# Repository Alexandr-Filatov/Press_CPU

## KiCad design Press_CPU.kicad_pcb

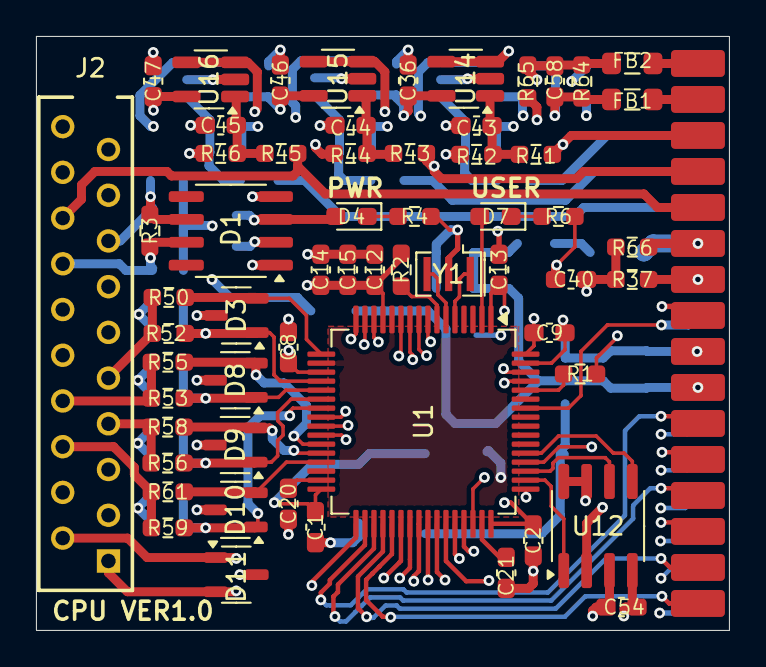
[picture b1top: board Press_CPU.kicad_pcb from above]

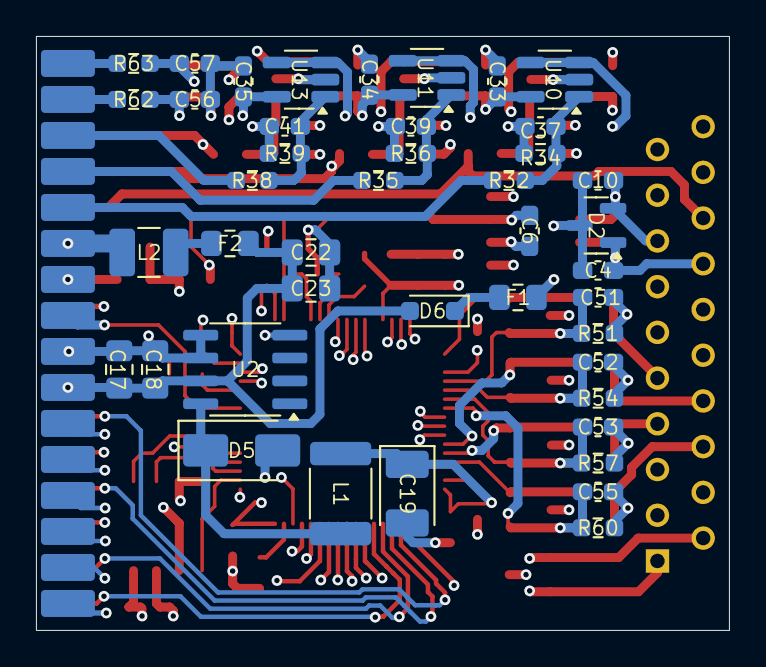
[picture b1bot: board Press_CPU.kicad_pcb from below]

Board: 6 copper layers, 38.5 x 33.0 mm, 104 parts (44 on the bottom side), 79 nets.

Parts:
C1, C2, C8, C9, C12, C13, C33, C34, C35, C36, C46, C47, C51, C52, C53, C55, C56, C57: 100n; C_0603_1608Metric_Pad1.08x0.95mm_HandSolder
C4, C10: 56p; C_0603_1608Metric_Pad1.08x0.95mm_HandSolder
C6, C20, C21, C58: 2.2u; C_0603_1608Metric_Pad1.08x0.95mm_HandSolder
C14: 4.7u; C_0603_1608Metric_Pad1.08x0.95mm_HandSolder
C15, C54: 1u; C_0603_1608Metric_Pad1.08x0.95mm_HandSolder
C17, C18, C22, C23: 10u; C_0805_2012Metric_Pad1.18x1.45mm_HandSolder
C19: 100u; CP_EIA-3528-21_Kemet-B_HandSolder
C37, C39, C40, C41, C43, C44, C45: 1n; C_0603_1608Metric_Pad1.08x0.95mm_HandSolder
D1: SOIC-8_3.9x4.9mm_P1.27mm
D2: SOT-23
D3, D8, D9, D10, D11: GSOT03C-E3-08; SOT-23-3
D4, D7: LED_0603_1608Metric_Pad1.05x0.95mm_HandSolder
D5: MBRA320; D_SMA
D6: D_Schottky_Small; D_SOD-323_HandSoldering
F1, F2: Fuse_Small; Fuse_0805_2012Metric_Pad1.15x1.40mm_HandSolder
FB1, FB2: BLM21AG102SN1D; L_0805_2012Metric_Pad1.05x1.20mm_HandSolder
J2: 2-215079-0; 22150790
J3, J4: Conn_01x16; PLD16_2.0mm
L1: 47u; L_1812_4532Metric_Pad1.30x3.40mm_HandSolder
L2: 2.2u; L_1210_3225Metric_Pad1.42x2.65mm_HandSolder
R1, R2, R6: 1k; R_0603_1608Metric_Pad0.98x0.95mm_HandSolder
R3: 120; R_0603_1608Metric_Pad0.98x0.95mm_HandSolder
R4: 750; R_0603_1608Metric_Pad0.98x0.95mm_HandSolder
R32, R35, R38, R41, R43, R45, R50, R52, R53, R55, R56, R58, R59, R61, R65: 1.8k; R_0603_1608Metric_Pad0.98x0.95mm_HandSolder
R34, R36, R37, R39, R42, R44, R46, R51, R54, R57, R60, R62, R63, R66: 3.6k; R_0603_1608Metric_Pad0.98x0.95mm_HandSolder
R64: 3.3k; R_0603_1608Metric_Pad0.98x0.95mm_HandSolder
U1: APM32F405RGT6; LQFP-64_10x10mm_P0.5mm
U2: LM2594HVM-3.3; SOIC-8_3.9x4.9mm_P1.27mm
U10, U11, U13, U14, U15, U16: LMV321; SOT-23-5_HandSoldering
U12: FM25W256; SOIC-8_3.9x4.9mm_P1.27mm
Y1: CSTCE8M00G55A-R0; Resonator_SMD_Murata_CSTxExxV-3Pin_3.0x1.1mm

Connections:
+3.3V: C1.1, C2.1, C6.2, C8.1, C9.1, C12.1, C13.1, C14.1, C15.1, C19.1, C33.1, C34.1, C35.1, C36.1, C46.1, C47.1, C54.1, D1.3 (Vcc), D4.2 (A), L1.2, R2.1, U1.1 (VBAT), U1.13 (VDDA), U1.19 (VDD), U1.32 (VDD), U1.48 (VDD), U1.64 (VDD), U2.4 (FB), U10.5 (V+), U11.5 (V+), U12.3 (~WP), U12.7 (~HOLD), U12.8 (VCC), U13.5 (V+), U14.5 (V+), U15.5 (V+), U16.5 (V+)
+5V: C17.1, C18.1, C22.1, C23.1, D6.2 (A), F2.1, J3.10, J4.7, U2.7 (VIN)
+5V_sense: J2.3, J2.10, J3.6, J4.11, L2.2, R65.1, R66.1
+5V_sense_MCU: C40.1, R37.1, R66.2, U1.8 (PC0)
AnalogIN1_MCU: C51.2, D3.1 (K), R51.1, R52.1, U1.20 (PA4)
AnalogIN2_MCU: C52.2, D8.1 (K), R53.1, R54.1, U1.21 (PA5)
AnalogIN3_MCU: C53.2, D9.1 (K), R56.1, R57.1, U1.22 (PA6)
AnalogIN4_MCU: C55.2, D10.1 (K), R59.1, R60.1, U1.23 (PA7)
BOOT0: R1.2, U1.60 (BOOT0)
BkIN: J4.9, U1.33 (PB12)
CAN1_RXD_MCU: D1.4 (R), U1.61 (PB8)
CAN1_TXD_MCU: D1.1 (D), U1.62 (PB9)
CANH: C4.2, D1.7 (CANH), D2.1 (K), J2.7, R3.2
CANL: C10.1, D1.6 (CANL), D2.2 (K), J2.6, R3.1
CAN_Power: F1.2, J2.8
Current_A: J3.5, R32.1
Current_A_MCU: U1.9 (PC1), U10.3 (-), U10.4
Current_B: J3.4, R35.1
Current_B_MCU: U1.10 (PC2), U11.3 (-), U11.4
Current_C: J3.3, R38.1
Current_C_MCU: U1.11 (PC3), U13.3 (-), U13.4
DigIN1_MCU: D3.2 (K), R50.2, U1.17 (PA3)
DigIN2_MCU: D8.2 (K), R55.2, U1.27 (PB1)
DigIN3_MCU: D9.2 (K), R58.2, U1.28 (PB2)
DigIN4_MCU: D10.2 (K), R61.2, U1.29 (PB10)
EEPROM_MISO_MCU: U1.52 (PC11), U12.2 (MISO)
EEPROM_MOSI_MCU: U1.53 (PC12), U12.5 (MOSI)
EEPROM_SCK_MCU: U1.51 (PC10), U12.6 (SCK)
EEPROM_~CS_MCU: U1.50 (PA15), U12.1 (~CS)
GND: C1.2, C2.2, C4.1, C6.1, C8.2, C9.2, C10.2, C12.2, C13.2, C14.2, C15.2, C17.2, C18.2, C19.2, C20.2, C21.2, C22.2, C23.2, C33.2, C34.2, C35.2, C36.2, C37.2, C39.2, C40.2, C41.2, C43.2, C44.2, C45.2, C46.2, C47.2, C51.1, C52.1, C53.1, C54.2, C55.1, C56.1, C57.1, C58.1, D1.2 (GND), D2.3 (A), D3.3 (A), D5.2 (A), D8.3 (A), D9.3 (A), D10.3 (A), D11.3 (A), FB1.2, J2.4, J2.9, J2.11, J2.18, J3.7, J3.9, J4.8, J4.10, R1.1, R4.2, R6.2, R34.2, R36.2, R37.2, R39.2, R42.2, R44.2, R46.2, R51.2, R54.2, R57.2, R60.2, R64.1, U1.12 (VSSA), U1.18 (VSS), U1.63 (VSS), U2.5 (~ON/OFF), U2.6 (GND), U10.2 (V-), U11.2 (V-), U12.4 (GND), U13.2 (V-), U14.2 (V-), U15.2 (V-), U16.2 (V-), Y1.2
Hall1: J2.1, J4.14, R41.1
Hall1_MCU: U1.15 (PA1), U14.3 (-), U14.4
Hall2: J2.2, J4.13, R43.1
Hall2_MCU: U1.16 (PA2), U15.3 (-), U15.4
Hall3: J2.5, J4.12, R45.1
Hall3_MCU: U1.14 (PA0), U16.3 (-), U16.4
IN/OUT1: J2.12, R50.1, R52.2
IN/OUT2: J2.13, R53.2, R55.1
IN/OUT3: J2.14, R56.2, R58.1
IN/OUT4: J2.15, R59.2, R61.1
NRST: R2.2, U1.7 (NRST)
unnamed: D4.1 (K), R4.1
unnamed: D5.1 (K), L1.1, U2.8 (OUT)
unnamed: D6.1 (K), F1.1
unnamed: D7.2 (A), U1.2 (PC13)
unnamed: D7.1 (K), R6.1
unnamed: F2.2, L2.1
unnamed: U1.5 (PH0), Y1.1
unnamed: U1.6 (PH1), Y1.3
unnamed: C20.1, U1.31 (VCAP_1)
unnamed: C21.1, U1.47 (VCAP_2)
unnamed: C37.1, R32.2, R34.1, U10.1 (+)
unnamed: C39.1, R35.2, R36.1, U11.1 (+)
unnamed: C41.1, R38.2, R39.1, U13.1 (+)
unnamed: C43.1, R41.2, R42.1, U14.1 (+)
unnamed: C44.1, R43.2, R44.1, U15.1 (+)
unnamed: C45.1, R45.2, R46.1, U16.1 (+)
PWM1_H: J3.11, U1.41 (PA8)
PWM1_L: J4.6, U1.34 (PB13)
PWM2_H: J3.13, U1.42 (PA9)
PWM2_L: J4.4, U1.35 (PB14)
PWM3_H: J3.15, U1.43 (PA10)
PWM3_L: J4.2, U1.36 (PB15)
SWCLK: D11.1 (K), J2.19, U1.49 (PA14)
SWDIO: D11.2 (K), J2.20, U1.46 (PA13)
Temp_mosfet_sense: J3.2, R62.1
Temp_mosfet_sense_MCU: C56.2, R62.2, U1.26 (PB0)
Temp_motor_GND: FB1.1, J4.15
Temp_motor_sense: FB2.1, J4.16
Temp_motor_sense_MCU: C58.2, FB2.2, R64.2, R65.2, U1.25 (PC5)
VBAT_sense: J3.1, R63.1
VBAT_sense_MCU: C57.2, R63.2, U1.24 (PC4)
f1H: J3.12, U1.44 (PA11)
f1L: J4.5, U1.45 (PA12)
f2H: J3.14, U1.39 (PC8)
f2L: J4.3, U1.40 (PC9)
f3H: J3.16, U1.38 (PC7)
f3L: J4.1, U1.37 (PC6)
uC_drv_en: J3.8, U1.58 (PB6)

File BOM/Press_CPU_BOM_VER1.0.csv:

"Reference","Value","Product Name","Replacement","Description P/N","Footprint","Qty","DNP"
"C1,C2,C8,C9,C12,C13,C33,C34,C35,C36,C46,C47,C51,C52,C53,C55,C56,C57","100n","","","","Capacitor_SMD:C_0603_1608Metric_Pad1.08x0.95mm_HandSolder","18",""
"C4,C10","56p","","","","Capacitor_SMD:C_0603_1608Metric_Pad1.08x0.95mm_HandSolder","2",""
"C6,C20,C21,C58","2.2u","","","","Capacitor_SMD:C_0603_1608Metric_Pad1.08x0.95mm_HandSolder","4",""
"C14","4.7u","","","","Capacitor_SMD:C_0603_1608Metric_Pad1.08x0.95mm_HandSolder","1",""
"C15,C54","1u","","","","Capacitor_SMD:C_0603_1608Metric_Pad1.08x0.95mm_HandSolder","2",""
"C17,C18,C22,C23","10u","","","","Capacitor_SMD:C_0805_2012Metric_Pad1.18x1.45mm_HandSolder","4",""
"C19","100u","","","","Capacitor_Tantalum_SMD:CP_EIA-3528-21_Kemet-B_HandSolder","1",""
"C37,C39,C40,C41,C43,C44,C45","1n","","","","Capacitor_SMD:C_0603_1608Metric_Pad1.08x0.95mm_HandSolder","7",""
"D1","~","SIT65HVD232DR","","CAN interface","Package_SO:SOIC-8_3.9x4.9mm_P1.27mm","1",""
"D2","~","PESD2CAN","","Dual Line CAN Bus Protector, 24Vrwm","Package_TO_SOT_SMD:SOT-23","1",""
"D3,D8,D9,D10,D11","~","GSOT03C-E3-08","","","Package_TO_SOT_SMD:SOT-23-3","5",""
"D4","~","FYLS-0805UYC","","Yellow LED","LED_SMD:LED_0603_1608Metric_Pad1.05x0.95mm_HandSolder","1",""
"D5","~","MBRA320","","","Diode_SMD:D_SMA","1",""
"D6","~","BAT46JFILM","","","Diode_SMD:D_SOD-323_HandSoldering","1",""
"D7","~","FYLS-0805UBC","","Blue LED","LED_SMD:LED_0603_1608Metric_Pad1.05x0.95mm_HandSolder","1",""
"F1,F2","~","MF-PSMF050X-2","","Fuse","Fuse:Fuse_0805_2012Metric_Pad1.15x1.40mm_HandSolder","2",""
"FB1,FB2","~","BLM21AG102SN1D","","","Inductor_SMD:L_0805_2012Metric_Pad1.05x1.20mm_HandSolder","2",""
"J2","~","2-215079-0","","","TE_my:22150790","1",""
"J3,J4","~","DS-1025-05 - 2x20","","","PLD_my:PLD16_2.0mm","2",""
"L1","47u","NLC453232T-470K-PF","","","Inductor_SMD:L_1812_4532Metric_Pad1.30x3.40mm_HandSolder","1",""
"L2","2.2u","CM322522-2R2KL","","","Inductor_SMD:L_1210_3225Metric_Pad1.42x2.65mm_HandSolder","1",""
"R1,R2,R6","1k","","","","Resistor_SMD:R_0603_1608Metric_Pad0.98x0.95mm_HandSolder","3",""
"R3","120","","","","Resistor_SMD:R_0603_1608Metric_Pad0.98x0.95mm_HandSolder","1",""
"R4","750","","","","Resistor_SMD:R_0603_1608Metric_Pad0.98x0.95mm_HandSolder","1",""
"R32,R35,R38,R41,R43,R45,R50,R52,R53,R55,R56,R58,R59,R61,R65","1.8k","","","","Resistor_SMD:R_0603_1608Metric_Pad0.98x0.95mm_HandSolder","15",""
"R34,R36,R37,R39,R42,R44,R46,R51,R54,R57,R60,R62,R63,R66","3.6k","","","","Resistor_SMD:R_0603_1608Metric_Pad0.98x0.95mm_HandSolder","14",""
"R64","3.3k","","","","Resistor_SMD:R_0603_1608Metric_Pad0.98x0.95mm_HandSolder","1",""
"U1","~","APM32F405RGT6","","","Package_QFP:LQFP-64_10x10mm_P0.5mm","1",""
"U2","~","LM2594HVM-3.3","","","Package_SO:SOIC-8_3.9x4.9mm_P1.27mm","1",""
"U10,U11,U13,U14,U15,U16","~","LMV321","","","Package_TO_SOT_SMD:SOT-23-5_HandSoldering","6",""
"U12","~","FM25W256","","","Package_SO:SOIC-8_3.9x4.9mm_P1.27mm","1",""
"Y1","~","CSTCE8M00G55A-R0","","","Crystal:Resonator_SMD_Murata_CSTxExxV-3Pin_3.0x1.1mm","1",""

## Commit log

2025-04-28 zero commit
2025-04-29 VER1.0: добавил гребенку
2025-05-19 VER1.0: добавил в разъём сигналы
2025-05-28 VER1.0: промежуточная трассировка
2025-05-30 VER1.0: проблема с пересечением EEPROM и аналоговыми входами
2025-06-01 VER1.0: попробовал развести по другому
2025-06-04 VER1.0: первая готовая трассировка, требует обсуждения
2025-06-10 VER1.0: добавил предохранители по питанию датчиков и внешнего CAN
2025-06-15 VER1.0: исправил дорожкт ШИМ
2025-06-16 VER1.0: добавил шелкографию с версией
2025-10-17 VER1.0: отредактировал бом и обновил лист закупки
